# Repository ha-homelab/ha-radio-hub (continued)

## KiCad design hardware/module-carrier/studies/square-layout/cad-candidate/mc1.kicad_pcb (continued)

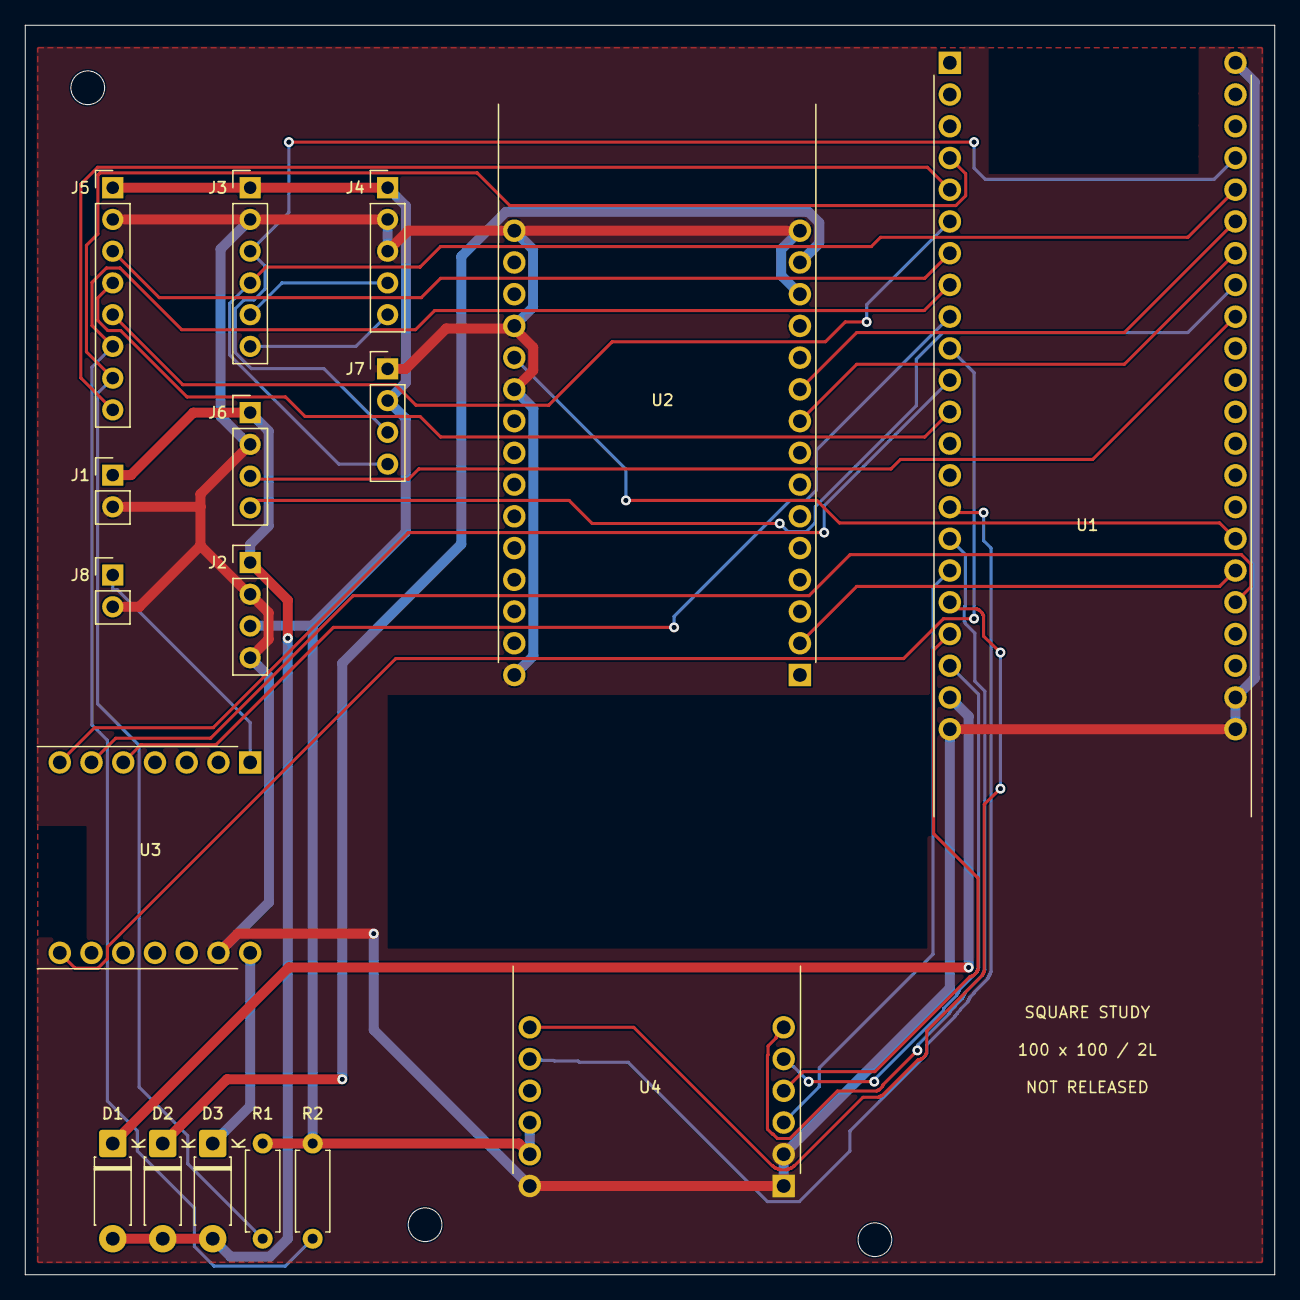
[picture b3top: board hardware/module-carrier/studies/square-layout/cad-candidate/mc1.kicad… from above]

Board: 2 copper layers, 100.0 x 100.0 mm, 20 parts (0 on the bottom side), 33 nets.

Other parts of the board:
H1, H2, H3: M2.5 NYLON NPTH

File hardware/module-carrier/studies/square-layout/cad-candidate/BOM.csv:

Reference,Quantity,Part / module,Carrier footprint,Side,Assembly note,Source
U1,1,ESP32-S3-DevKitC-1-N8R8 v1.1,MC1:S3_DevKitC1_v11,Top,Factory male headers solder directly; 3V3 outputs NC; USB19/20 and bridge43/44 untouched; no sockets,https://dl.espressif.com/dl/schematics/esp_idf/DXF_ESP32-S3-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
U2,1,ESP32-H2-DevKitM-1-N4S,MC1:H2_DevKitM1,Top,RCP RX4 TX5; native USB and UART bridge pins untouched; 3V3/VBAT NC,https://dl.espressif.com/dl/schematics/esp32-h2-devkitm-1_v1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
U3,1,Seeed XIAO MG24 pre-soldered 102010690,MC1:XIAO_MG24,Top,External UART PC06/PC07; CTS PC04 RTS PC05; USB probe preserved; 3V3 OUT NC,https://files.seeedstudio.com/wiki/XIAO_MG24/Getting_Start/X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
U4,1,WIZ850io finished module,MC1:WIZ850io,Top,Direct factory pins; two1x6 at20.32 rowspacing; RJ45 faces BOTTOM with mouth y=102mm; NO PoE extraction;3.3V only,https://docs.wiznet.io/img/products/wiz850io/wiz850io_dimension.png
J1,1,FUSED ISOLATED 5V INPUT,MC1:PinHeader_1x02_P2.54mm_Vertical,Top,Offboard assembled active PoE splitter and fused 5V harness. No raw PoE voltage on carrier.,https://www.samtec.com/products/tsw
J2,1,D24V22F3 external assembled buck,MC1:PinHeader_1x04_P2.54mm_Vertical,Top,Harness interface only; pin1 buckVIN; pin2GND;pin3buckVOUT;pin4GND. Buck remains separate ready module.,https://www.samtec.com/products/tsw
J3,1,DFR0627 WK2132 ready module harness,MC1:PinHeader_1x06_P2.54mm_Vertical,Top,"Harness to DFR0627 I2C and UART1, no WK2132 SMD on carrier. J3.5=module TX1;J3.6=module RX1; IA1=1 IA0=1; register address 0x70, FIFO 0x71; verify physical markings.",https://wiki.dfrobot.com/dfr0627
J4,1,ZAC93 ready module harness,MC1:PinHeader_1x05_P2.54mm_Vertical,Top,Carrier1->ZACpin1;2->pin6;3->pin9;4->pin8RX;5->pin10TX. Different from ZAC physical header layout.,https://www.samtec.com/products/tsw
J5,1,CC1101 ready module harness,MC1:PinHeader_1x08_P2.54mm_Vertical,Top,3.3V; GDO0 open-drain TX with external4.7k pullup; GDO2 receiver.,https://www.samtec.com/products/tsw
J6,1,LD2450 radar harness,MC1:PinHeader_1x04_P2.54mm_Vertical,Top,Carrier3->radarRX;carrier4<-radarTX;5V supply;3.3V data.,https://www.samtec.com/products/tsw
J7,1,BME680 external pod harness,MC1:PinHeader_1x04_P2.54mm_Vertical,Top,"External pod,1GND2VDD3SDA4SCL;I2C pullups on modules;do notaddunreviewedpullups.",https://www.samtec.com/products/tsw
D1,1,1N5819 USB supply isolation,MC1:D_DO-41_SOD81_P7.62mm_Horizontal,Top,Cathodepad1->board5V;anodepad2->fused5Vbus. VerifyUSBprogrammingpowerpaths;forwarddropheadroom.,https://www.vishay.com/docs/88525/1n5817.pdf
D2,1,1N5819 USB supply isolation,MC1:D_DO-41_SOD81_P7.62mm_Horizontal,Top,Cathodepad1->board5V;anodepad2->fused5Vbus. VerifyUSBprogrammingpowerpaths;forwarddropheadroom.,https://www.vishay.com/docs/88525/1n5817.pdf
D3,1,1N5819 USB supply isolation,MC1:D_DO-41_SOD81_P7.62mm_Horizontal,Top,Cathodepad1->board5V;anodepad2->fused5Vbus. VerifyUSBprogrammingpowerpaths;forwarddropheadroom.,https://www.vishay.com/docs/88525/1n5817.pdf
R1,1,4.7k RF GDO0 pull-up,MC1:R_Axial_DIN0207_L6.3mm_D2.5mm_P7.62mm_Horizontal,Top,,https://www.vishay.com/docs/28729/mrs16.pdf
R2,1,10k RF CS idle pull-up,MC1:R_Axial_DIN0207_L6.3mm_D2.5mm_P7.62mm_Horizontal,Top,,https://www.vishay.com/docs/28729/mrs16.pdf
J8,1,XIAO BOOT service short to GND,MC1:PinHeader_1x02_P2.54mm_Vertical,Top,Temporary short D0/PC00 to GND while resetting XIAO for recovery. Normally OPEN.,https://www.samtec.com/products/tsw

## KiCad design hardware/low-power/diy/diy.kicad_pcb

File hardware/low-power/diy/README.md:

# LP-D0: single-sided, wire-assisted DIY carrier

<!-- MC2-CURRENT-DESIGN -->
> **Current build: [MC2 — three external antennas](../../../docs/external-antennas.md).** This page retains an earlier design or evaluation for reference. Its board images, pin maps, enclosure fit and alternative BOMs are not the current MC2 build.

LP-D0 is a prototype for laser toner transfer and manual drilling. It implements the LP-P0 electrical contract on a 190 × 145 mm low-voltage backplane. The required assembly includes bottom copper **and insulated wire links**. It is not a one-layer redesign of the RF modules themselves, and no assembled D0 has been electrically tested yet.

The board accepts only isolated, regulated 5 V. The PoE front end and Pololu D24V22F3 regulator stay external. Never connect an Ethernet PoE pair or 48 V to this PCB. The nominal design ceiling remains 1 A at the 5 V input; actual startup voltage drop and temperature must be measured.

## What can be made with toner transfer

D0 uses 0.6 mm signal tracks, 1.2 mm supply/return tracks, nominal 0.5 mm copper clearance, and 2 mm through-hole lands. All copper tracks are on B.Cu. KiCad represents through-hole pads with annuli on both outer layers; **only the bottom annuli are fabricated**. There are no plated vias, no hidden top copper traces, and no electrical dependence on hole plating. Through-hole components and T-numbered wire holes are soldered on the copper side. The explicitly identified E-numbered joints instead solder to exposed raised-adapter header pins above the board; they do not add a drilled hole.

C0 is a two-layer, mixed SMT/through-hole carrier; printing only its bottom layer would omit connections. M0 has a fine-pitch MGM240P footprint, ground planes and an antenna keepout: order it from a PCB manufacturer. I0 is a four-layer integrated design and is unsuitable for this home process. Existing enclosure mounting patterns do not match D0.

## Purchased fine-pitch assemblies are still necessary

- U1 is SC16IS752IPW,128 soldered to the **TSSOP side** of an [Adafruit 1208 adapter](https://www.adafruit.com/product/1208), with two 14-pin headers. Looking at the populated TSSOP face, pin 1 is upper-left, pin 14 lower-left, pin 15 lower-right and pin 28 upper-right. Row separation is 15.24 mm and pitch 2.54 mm. The blank adapter does not include the IC or headers.
- U2 is TPS3808G33DBVR on the SOT23-6 side of an [Adafruit 1230 adapter](https://www.adafruit.com/product/1230), with two 3-pin headers. Pin1/2/3 run down the left; 6/5/4 down the right. Row separation 7.62 mm; pitch 2.54 mm. Do not populate the two reverse-side transistor sites. Stock may vary; a different adapter requires matching its pin map and dimensions.
- Keep both adapter PCBs at least 6 mm above D0; some insulated links may pass underneath. Fit and inspect these links before soldering the adapter in place. Use [Adafruit 400 extra-long headers](https://www.adafruit.com/product/400), cut to two 14-pin and two 3-pin lengths (one five-strip pack supplies both adapters). Its [manufacturer drawing](https://cdn-shop.adafruit.com/datasheets/18072.pdf) specifies 0.64 mm square pins, 7.73 mm on each side of a 2.54 mm insulator. Rest the insulator on D0, set the adapter underside 6 mm above D0, solder and trim the long tails. Availability must be checked before ordering.
- The populated [M0 adapter](../carrier/mg24-adapter/README.md) is mandatory for MGM240PA22VNA3. It contains the module decoupling, BOOT and SWD service connections. A bare MGM240P cannot plug into J6.
- S3/H2 development boards, WIZ850io, ZAC93, CC1101, LD2450 and BME680 connect through the named harnesses. This PCB does not invent pin positions for unknown module revisions. Use the verified GPIO/net labels, not guessed connector geometry.

The adapter mating geometry was checked against [Adafruit's published CAD at a fixed commit](https://github.com/adafruit/Adafruit-SMT-Breakout-PCBs/tree/dbd7a1928c2b668a9edf3d53277063eac4c3e938). U1/U2 still require fine-pitch soldering by the builder or an assembly service. The household-iron process applies to D0 alone.

## Files and assembly

- `diy.kicad_sch`, `diy.kicad_pcb`, `diy.kicad_pro`: native connected assembly schematic and PCB.
- `logical-netlist.json`: original electrical net names and physical part pins.
- `assembly-netlist.json`: bottom-copper islands plus actual off-board wire components W1…Wn.
- `connectors.json`: every connector pin, remote destination and actual board coordinates.
- `assembly-bom.csv`, `harness-bom.csv`: board parts, adapters, mating housings, contacts and materials.
- `jumpers.json`, `jumpers.csv`: every insulated link, AWG, terminal holes, route and cut length. The route is a top-view assembly guide, not copper artwork.
- `drill.csv`: all manually drilled holes in top-view coordinates.
- `print/`: printable transfer, inspection, drilling and assembly documents generated by the dedicated print exporter.

J1–J9 preserve C0's electrical pin numbering. J3 is **not a Raspberry Pi GPIO connector**. J10 changes physically from JST SH to through-hole JST XH, retaining 1=GND / 2=+3V3 / 3=SDA / 4=SCL. Splice to a factory QT cable and continuity-test each conductor. Every cable mating-face view is mirrored relative to the PCB component view; use molded circuit numbers and the square pin 1 land.

For F1 use Littelfuse 022901.5MXP, a 1.5 A slow-blow 2AG cartridge, in the external 01500274Z holder. Adapt the holder's 16 AWG leads to short 22 AWG insulated tails for the 1.1 mm F1 holes; cover the splices and strain-relieve the holder. The manufacturer [catalog](https://www.littelfuse.com/assetdocs/powr-gard-catalog?assetguid=85d36235-a32b-4608-bfed-f9878aa43af0) identifies the 229 series’ 125 VDC rating. The [holder datasheet](https://www.littelfuse.com/assetdocs/fuse-holder-150-datasheet?assetguid=662e5ae4-2c3a-4d7a-8642-e7d9db02703d) specifies 2AG/5×20 compatibility. This does not change D0's **5 V-only** input limit.

Use insulated AWG 24 for power/return jumpers and AWG 26 for signal links. At most two stripped ends share a 1.1 mm terminal hole; trial-fit wire and drill before making the whole board. The cut schedule includes the projected routed length plus 14 mm, with an additional 4 mm for each raised E joint; strip 5 mm at each end and trim the solder tails after assembly. Do not use bare jumpers where paths cross. Keep insulation against the board, avoiding conductive contact with headers, adapter pads or other wires. Support externally connected wires so a pull cannot lift a copper land.

E-numbered endpoints identify a specific U1/U2 header pin, not a new pad. Solder a single wire to its exposed shaft at **4 mm above D0**, before placing the adapter at its required **6 mm underside height**. The first/last 3 mm of that wire passes over the header insulator at the raised height, then descends. Keep the joint compact, insulated from adjacent pins and strain-relieved. Confirm the actual 2 mm space below the daughterboard is sufficient for the joint and wire before final soldering; this fit is not yet physically tested. The board-level adapter courtyards represent the header strips, while assembly drawings retain the full elevated board outlines.

## Firmware and physical acceptance

No GPIO or serial assignment changes. The supplied low-power firmware currently uses 10 MHz W5500 SPI and 4 MHz for the shared CC1101/SC16 bus. D0 has no controlled-impedance routing or ground plane; clock frequencies are not proof that its assembled wires will be reliable. Keep external SPI harnesses at or below an initial 50 mm, retain the interleaved returns in J3, pair each clock/data group with a short return, and measure SPI edges and error behavior with the full load. This starting length is a prototype constraint, not a validated signal-integrity guarantee. The 3 W AC objective is also unmeasured for D0. If a lower SPI rate is required, use an explicit D0 configuration change and repeat the firmware build and throughput tests; do not silently edit the common profile.

Before installing modules: inspect the toner result under magnification; verify no copper bridges; continuity-test all nets against the schematic, including every W link; check 5 V/3.3 V/GND isolation; confirm F1 and regulator polarity. Power from a current-limited 5 V source first, verify 3.3 V at every connector, then add modules in stages. Check U1 crystal startup, its 115200 baud UART, IRQ handling, H2 reset/BOOT, Zigbee RTS/CTS and CC1101 transmit/receive arbitration. Repeat the existing hub acceptance tests with the final enclosure and radios active. Radio antenna spacing and the M0 keepout remain unchanged.

A passed CAD check cannot establish toner adhesion, actual etched track width, hand-drilled annular rings, solder quality, antenna performance, regulatory compliance or production readiness. The board is a workshop prototype, not a validated product for sale.

## Reproduce and validate

Run from the repository root with KiCad 10's Python (which supplies `pcbnew`):

```sh
python3 hardware/low-power/diy/generate.py
python3 -m unittest discover -s hardware/low-power/diy -p 'test_*.py'
python3 hardware/low-power/diy/validate.py --kicad-cli kicad-cli --check-hashes --out /tmp/d0-check
```

`routing-plan.json` is the reviewed geometric input. Regeneration uses it directly and never reruns an autorouter. Optional route-authoring tools are `prepare.py`, `capture_routing.py`, `plan_wires.py` and `complete_wires.py`; they write exploratory files under ignored `.build/`. Their intermediate F.Cu geometry must never be sent to a fabricator or printed for transfer. The final validator calculates copper contact from the actual PCB, joins only the numbered assembly wires, and compares the result to the original pin-level contract. Native ERC/DRC alone is insufficient because an intentionally split island net can be internally connected while the required physical wire is missing.

The released D0 snapshot has 636 bottom tracks, 100 dedicated wire holes, 54 insulated links and one raised joint E1 at U1.11. Native ERC, DRC, schematic parity and unconnected checks report zero violations. The independent graph verifies all 195 component pins across 44 logical nets. These are CAD results, not measurements of a constructed board.

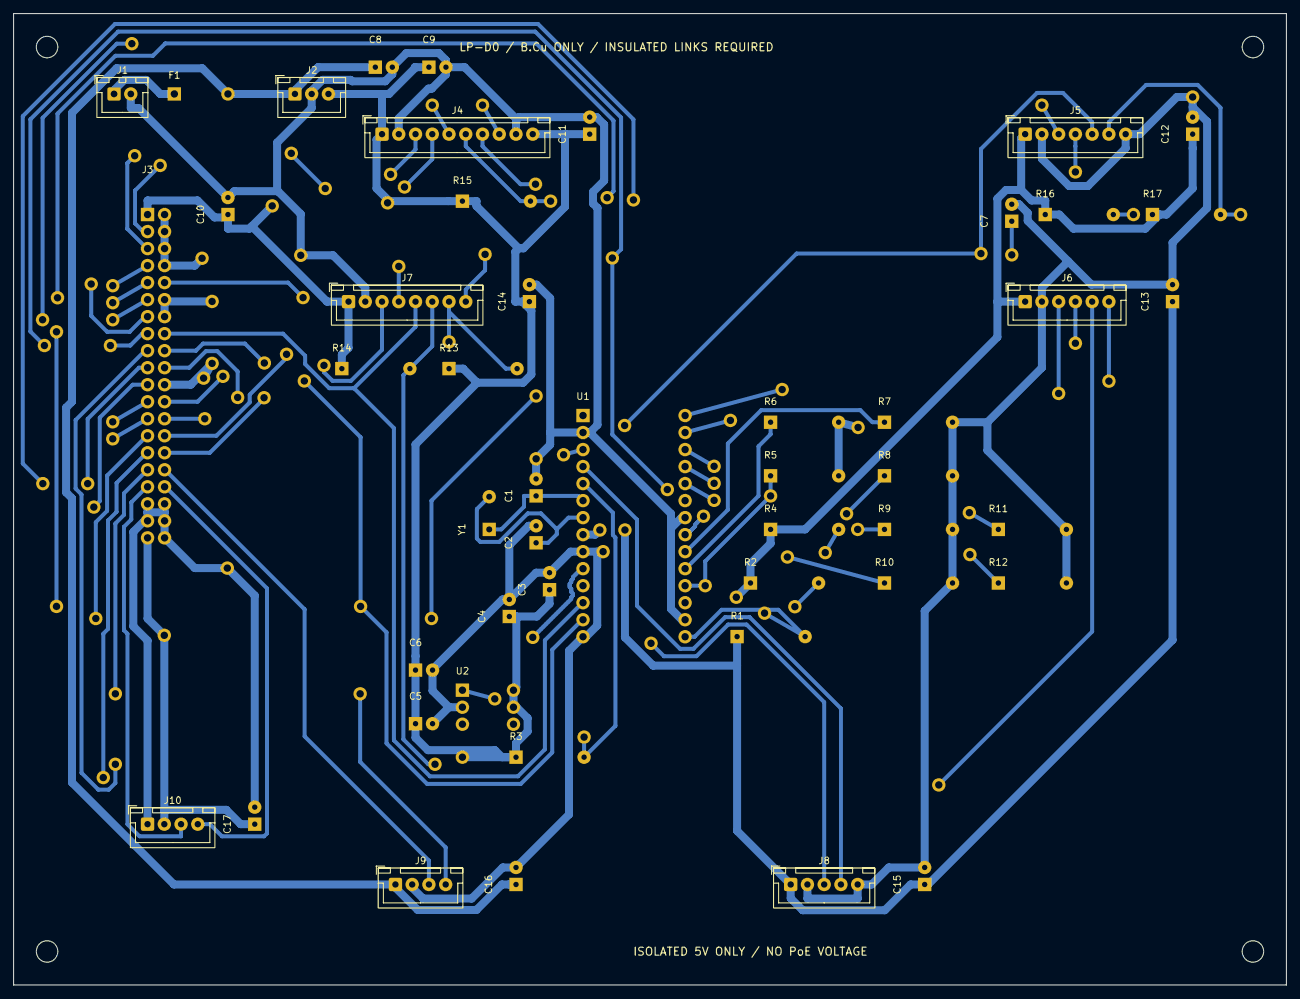
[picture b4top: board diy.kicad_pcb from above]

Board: 2 copper layers, 190.0 x 145.0 mm, 152 parts (0 on the bottom side), 97 nets.

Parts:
C1: 22pF; Radial_C_P2.54
C2: 33pF; Radial_C_P2.54
C3, C5, C10, C11, C12, C13, C14, C15, C16, C17: 100nF; Radial_C_P2.54
C4, C7: 1uF; Radial_C_P2.54
C6: 1nF; Radial_C_P2.54
C8, C9: 22uF; Radial_C_P2.54
F1: Littelfuse 022901.5MXP; FuseHarness
H1, H2, H3, H4: M3 manually drilled
J1: B2B-XH-A; JST_XH_B2B-XH-A_1x02_P2.50mm_Vertical
J2: B3B-XH-A; JST_XH_B3B-XH-A_1x03_P2.50mm_Vertical
J3: 61204021621; Wurth_61204021621
J4: B10B-XH-A; JST_XH_B10B-XH-A_1x10_P2.50mm_Vertical
J5: B7B-XH-A; JST_XH_B7B-XH-A_1x07_P2.50mm_Vertical
J6: B6B-XH-A; JST_XH_B6B-XH-A_1x06_P2.50mm_Vertical
J7: B8B-XH-A; JST_XH_B8B-XH-A_1x08_P2.50mm_Vertical
J8: B5B-XH-A; JST_XH_B5B-XH-A_1x05_P2.50mm_Vertical
J9, J10: B4B-XH-A; JST_XH_B4B-XH-A_1x04_P2.50mm_Vertical
R1: 1k; Axial_R_P10.16
R2, R3, R4, R14, R15, R16, R17: 10k; Axial_R_P10.16
R5, R6, R7, R8, R9, R10, R11, R12: 100k; Axial_R_P10.16
R13: 4.7k; Axial_R_P10.16
T1, T2, T3, T4, T5, T6, T7, T8, T9, T10, T11, T12, T13, T14, T15, T16, T17, T18, T19, T20, T21, T22, T23, T24, T25, T26, T27, T28, T29, T30, T31, T32, T33, T34, T35, T36, T37, T38, T39, T40, T41, T42, T43, T44, T45, T46, T47, T48, T49, T50, T51, T52, T53, T54, T55, T56, T57, T58, T59, T60, T61, T62, T63, T64, T65, T66, T67, T68, T69, T70, T71, T72, T73, T74, T75, T76, T77, T78, T79, T80, T81, T82, T83, T84, T85, T86, T87, T88, T89, T90, T91, T92, T93, T94, T95, T96, T97, T98, T99, T101: Insulated wire terminal hole; WireTerminal
U1: SC16IS752IPW,128; Adafruit1208_TSSOP28
U2: TPS3808G33DBVR; Adafruit1230_SOT23_6
Y1: AB-3.6864MHZ-B2; HC49U

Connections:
/+3V3__1: C10.1, J3.1, J7.1, R14.1, T2.1
/+3V3__2: C3.1, C4.1, C5.1, C6.1, C9.1, C11.1, C14.1, J2.3, J4.1, J4.10, R3.1, R13.1, R15.1, T3.1, T79.1, U2.5, U2.6
/+3V3__3: C12.1, J5.1, J6.1, R2.1, R4.1, R16.1, R17.1, T78.1
/+3V3__4: C13.1, C15.1, J8.1, R1.1, T5.1
/+3V3__5: C17.1, J3.39, J10.2, T1.1
/+3V3__6: T4.1, U1.8
/+5V_IN__1: F1.1, J1.1
/+5V__1: C8.1, C16.1, F1.2, J2.1, J9.1
/GND__1: C1.2, C8.2, C9.2, C10.2, C11.2, C14.2, J1.2, J2.2, J4.2, J4.9, J7.2, T10.1, T11.1, U1.2, U1.16, U1.22
/GND__2: C7.2, C12.2, C13.2, C15.2, J5.2, J5.7, J6.2, J8.2, J8.5, R7.2, R8.2, R9.2, R10.2, R11.2, R12.2, T13.1
/GND__3: C2.2, C3.2, C4.2, C5.2, C6.2, C16.2, J9.2, T12.1, U1.9, U1.14, U2.2
/GND__4: C17.2, J3.35, J3.36, J3.37, J3.38, J3.40, J10.1, T9.1
/GND__5: J3.12, J3.14, T7.1
/GND__6: J3.2, J3.4, J3.6, J3.8, T6.1
/GND__7: J3.22, T8.1, T81.1
/GND__8: R5.2, R6.2, T80.1
/bme680_scl__1: J3.34, J10.4
/bme680_sda__1: J3.33, J10.3
/cc1101_cs__1: J3.17, T14.1
/cc1101_cs__2: J7.6, R14.2, T15.1
/cc1101_gdo0_tx__1: J3.18, T16.1
/cc1101_gdo0_tx__2: J7.7, R13.2, T82.1
/cc1101_gdo2_rx__1: J3.19, T18.1
/cc1101_gdo2_rx__2: J7.8, T19.1
/cc1101_gdo2_rx__3: T17.1, T20.1
/gpio0_unused__1: R5.1, T21.1, T22.1, U1.18
/gpio1_unused__1: R6.1, U1.19
/gpio2_unused__1: R7.1, U1.20
/gpio3_unused__1: R8.1, T83.1
/gpio3_unused__2: T84.1, U1.21
/gpio4_unused__1: R9.1, T85.1
/gpio4_unused__2: T86.1, U1.25
/gpio5_unused__1: R10.1, T87.1
/gpio5_unused__2: T88.1, U1.26
/gpio6_unused__1: R11.1, T89.1
/gpio6_unused__2: T90.1, U1.27
/gpio7_unused__1: R12.1, T91.1
/gpio7_unused__2: T92.1, U1.28
/h2_boot__1: J3.26, T23.1
/h2_boot__2: J5.6, R17.2, T24.1
/h2_reset__1: C7.1, T28.1
/h2_reset__2: J3.25, T25.1
/h2_reset__3: J5.5, T26.1, T27.1
/h2_reset__4: R16.2, T29.1
/h2_rx__1: J3.24, T30.1
/h2_rx__2: J5.4, T31.1
/h2_tx__1: J3.23, T32.1
/h2_tx__2: J5.3, T33.1
/ld2450_rx__1: J3.32, J9.3
/ld2450_tx__1: J3.31, T34.1
/ld2450_tx__2: J9.4, T35.1
/mg24_cts__1: J3.30, T36.1
/mg24_cts__2: J6.6, T37.1
/mg24_rts__1: J3.29, T38.1
/mg24_rts__2: J6.5, T39.1
/mg24_rx__1: J3.28, T40.1
/mg24_rx__2: J6.4, T41.1
/mg24_tx__1: J3.27, T42.1
/mg24_tx__2: J6.3, T45.1
/mg24_tx__3: T43.1, T44.1
/rxb_unused__1: R4.2, T93.1
/rxb_unused__2: T94.1, U1.24
/sc16_cs__1: J3.20, T46.1
/sc16_cs__2: R2.2, T95.1
/sc16_cs__3: T96.1, U1.10
/sc16_irq__1: J3.21, T47.1
/sc16_irq__2: R1.2, T97.1, U1.15
/sc16_reset__1: R3.2, T98.1, U1.5
/sc16_reset__2: T99.1, U2.1
/shared_spi_miso__1: J3.16, J7.5, U1.12
/shared_spi_mosi__1: J3.15, T49.1
/shared_spi_mosi__2: J7.4, T50.1
/shared_spi_mosi__4: T48.1, T51.1, T52.1
/shared_spi_sclk__1: J3.13, T55.1
/shared_spi_sclk__2: J7.3, T57.1
/shared_spi_sclk__3: T56.1, T58.1, U1.13
/shared_spi_sclk__4: T53.1, T54.1
/w5500_cs__1: J3.9, T60.1
/w5500_cs__2: J4.6, R15.2, T61.1
/w5500_cs__3: T59.1, T62.1
/w5500_irq__1: J3.10, T63.1
/w5500_irq__2: J4.7, T64.1
/w5500_miso__1: J3.7, T65.1
/w5500_miso__2: J4.5, T66.1
/w5500_mosi__1: J3.5, T67.1
/w5500_mosi__2: J4.4, T70.1
/w5500_mosi__3: T68.1, T69.1
/w5500_reset__1: J3.11, T72.1
/w5500_reset__2: J4.8, T74.1
/w5500_reset__3: T71.1, T73.1
/w5500_sclk__1: J3.3, T75.1
/w5500_sclk__2: J4.3, T76.1
/xtal1__1: C1.1, U1.6, Y1.1
/xtal2__1: C2.1, U1.7, Y1.2
/zac93_rx__1: J8.4, U1.4
/zac93_tx__1: J8.3, T77.1
/zac93_tx__2: T101.1, U1.3

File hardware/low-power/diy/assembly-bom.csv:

Reference,Quantity,Manufacturer part / value,Footprint,Note,Source
J1,1,B2B-XH-A,Connector_JST:JST_XH_B2B-XH-A_1x02_P2.50mm_Vertical,Isolated regulated 5V input,https://www.jst-mfg.com/product/pdf/eng/eXH.pdf
J2,1,B3B-XH-A,Connector_JST:JST_XH_B3B-XH-A_1x03_P2.50mm_Vertical,External D24V22F3 buck,https://www.jst-mfg.com/product/pdf/eng/eXH.pdf
J3,1,61204021621,DIY:Wurth_61204021621,S3 keyed 40-position IDC harness; NOT Raspberry Pi compatible,https://www.we-online.com/components/products/datasheet/6120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
J4,1,B10B-XH-A,Connector_JST:JST_XH_B10B-XH-A_1x10_P2.50mm_Vertical,WIZ850io Ethernet module,https://www.jst-mfg.com/product/pdf/eng/eXH.pdf
J5,1,B7B-XH-A,Connector_JST:JST_XH_B7B-XH-A_1x07_P2.50mm_Vertical,H2 Thread RCP,https://www.jst-mfg.com/product/pdf/eng/eXH.pdf
J6,1,B6B-XH-A,Connector_JST:JST_XH_B6B-XH-A_1x06_P2.50mm_Vertical,MG24 Zigbee NCP,https://www.jst-mfg.com/product/pdf/eng/eXH.pdf
J7,1,B8B-XH-A,Connector_JST:JST_XH_B8B-XH-A_1x08_P2.50mm_Vertical,CC1101 RF module,https://www.jst-mfg.com/product/pdf/eng/eXH.pdf
J8,1,B5B-XH-A,Connector_JST:JST_XH_B5B-XH-A_1x05_P2.50mm_Vertical,ZAC93 Z-Wave module,https://www.jst-mfg.com/product/pdf/eng/eXH.pdf
J9,1,B4B-XH-A,Connector_JST:JST_XH_B4B-XH-A_1x04_P2.50mm_Vertical,LD2450 radar,https://www.jst-mfg.com/product/pdf/eng/eXH.pdf
J10,1,B4B-XH-A,Connector_JST:JST_XH_B4B-XH-A_1x04_P2.50mm_Vertical,"TH XH to factory STEMMA QT cable; same logical order as C0, mechanically NOT a QT socket.",https://www.jst-mfg.com/product/pdf/eng/eXH.pdf
F1,1,Littelfuse 022901.5MXP,DIY:FuseHarness,1.5A slow-blow 2AG cartridge in external01500274Z holder. Holder leads adapt to22AWG at F1 holes; insulate splices. <=1A continuous design. Do not bridge.,https://www.littelfuse.com/assetdocs/powr-gard-catalog?asset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
U1,1,"SC16IS752IPW,128",DIY:Adafruit1208_TSSOP28,"SC16IS752IPW,128 soldered to factory Adafruit1208 TSSOP side; pin1 adapter orientation verified from published CAD; no SOIC chip. Solder 2x14 male headers to adapter.",https://www.adafruit.com/product/1208
U2,1,TPS3808G33DBVR,DIY:Adafruit1230_SOT23_6,"TPS3808G33DBVR soldered to factory Adafruit1230 SOT23-6 adapter, two 1x3 male headers. Do not populate reverse-side transistor footprints.",https://www.adafruit.com/product/1230
Y1,1,AB-3.6864MHZ-B2,DIY:HC49U,"Through-hole HC49/U 3.6864MHz18pF; 4.88mm lead pitch; initial22/33pF loads, validate oscillation/frequency on hardware.",https://abracon.com/Resonators/ab.pdf
R1,1,1k,DIY:Axial_R_P10.16,"Axial 1%0.25W resistor, body<=6.8x2.5mm, leads formed to10.16mm pitch.",
R2,1,10k,DIY:Axial_R_P10.16,"Axial 1%0.25W resistor, body<=6.8x2.5mm, leads formed to10.16mm pitch.",
R3,1,10k,DIY:Axial_R_P10.16,"Axial 1%0.25W resistor, body<=6.8x2.5mm, leads formed to10.16mm pitch.",
R4,1,10k,DIY:Axial_R_P10.16,"Axial 1%0.25W resistor, body<=6.8x2.5mm, leads formed to10.16mm pitch.",
R5,1,100k,DIY:Axial_R_P10.16,"Axial 1%0.25W resistor, body<=6.8x2.5mm, leads formed to10.16mm pitch.",
R6,1,100k,DIY:Axial_R_P10.16,"Axial 1%0.25W resistor, body<=6.8x2.5mm, leads formed to10.16mm pitch.",
R7,1,100k,DIY:Axial_R_P10.16,"Axial 1%0.25W resistor, body<=6.8x2.5mm, leads formed to10.16mm pitch.",
R8,1,100k,DIY:Axial_R_P10.16,"Axial 1%0.25W resistor, body<=6.8x2.5mm, leads formed to10.16mm pitch.",
R9,1,100k,DIY:Axial_R_P10.16,"Axial 1%0.25W resistor, body<=6.8x2.5mm, leads formed to10.16mm pitch.",
R10,1,100k,DIY:Axial_R_P10.16,"Axial 1%0.25W resistor, body<=6.8x2.5mm, leads formed to10.16mm pitch.",
R11,1,100k,DIY:Axial_R_P10.16,"Axial 1%0.25W resistor, body<=6.8x2.5mm, leads formed to10.16mm pitch.",
R12,1,100k,DIY:Axial_R_P10.16,"Axial 1%0.25W resistor, body<=6.8x2.5mm, leads formed to10.16mm pitch.",
R13,1,4.7k,DIY:Axial_R_P10.16,"Axial 1%0.25W resistor, body<=6.8x2.5mm, leads formed to10.16mm pitch.",
R14,1,10k,DIY:Axial_R_P10.16,"Axial 1%0.25W resistor, body<=6.8x2.5mm, leads formed to10.16mm pitch.",
R15,1,10k,DIY:Axial_R_P10.16,"Axial 1%0.25W resistor, body<=6.8x2.5mm, leads formed to10.16mm pitch.",
R16,1,10k,DIY:Axial_R_P10.16,"Axial 1%0.25W resistor, body<=6.8x2.5mm, leads formed to10.16mm pitch.",
R17,1,10k,DIY:Axial_R_P10.16,"Axial 1%0.25W resistor, body<=6.8x2.5mm, leads formed to10.16mm pitch.",
C1,1,22pF,DIY:Radial_C_P2.54,"Radial ceramic >=10V, body<=5x3mm, C0G for crystal loads; X7R otherwise. Form leads to2.54mm pitch; no adjacent lead shorts.",
C2,1,33pF,DIY:Radial_C_P2.54,"Radial ceramic >=10V, body<=5x3mm, C0G for crystal loads; X7R otherwise. Form leads to2.54mm pitch; no adjacent lead shorts.",
C3,1,100nF,DIY:Radial_C_P2.54,"Radial ceramic >=10V, body<=5x3mm, C0G for crystal loads; X7R otherwise. Form leads to2.54mm pitch; no adjacent lead shorts.",
C4,1,1uF,DIY:Radial_C_P2.54,"Radial ceramic >=10V, body<=5x3mm, C0G for crystal loads; X7R otherwise. Form leads to2.54mm pitch; no adjacent lead shorts.",
C5,1,100nF,DIY:Radial_C_P2.54,"Radial ceramic >=10V, body<=5x3mm, C0G for crystal loads; X7R otherwise. Form leads to2.54mm pitch; no adjacent lead shorts.",
C6,1,1nF,DIY:Radial_C_P2.54,"Radial ceramic >=10V, body<=5x3mm, C0G for crystal loads; X7R otherwise. Form leads to2.54mm pitch; no adjacent lead shorts.",
C7,1,1uF,DIY:Radial_C_P2.54,"Radial ceramic >=10V, body<=5x3mm, C0G for crystal loads; X7R otherwise. Form leads to2.54mm pitch; no adjacent lead shorts.",
C8,1,22uF,DIY:Radial_C_P2.54,"22uF >=10V radial electrolytic, body<=5mm, pin1 positive. Form leads to2.54mm pitch; no adjacent lead shorts.",
C9,1,22uF,DIY:Radial_C_P2.54,"22uF >=10V radial electrolytic, body<=5mm, pin1 positive. Form leads to2.54mm pitch; no adjacent lead shorts.",
C10,1,100nF,DIY:Radial_C_P2.54,"Radial ceramic >=10V, body<=5x3mm, C0G for crystal loads; X7R otherwise. Form leads to2.54mm pitch; no adjacent lead shorts.",
C11,1,100nF,DIY:Radial_C_P2.54,"Radial ceramic >=10V, body<=5x3mm, C0G for crystal loads; X7R otherwise. Form leads to2.54mm pitch; no adjacent lead shorts.",
C12,1,100nF,DIY:Radial_C_P2.54,"Radial ceramic >=10V, body<=5x3mm, C0G for crystal loads; X7R otherwise. Form leads to2.54mm pitch; no adjacent lead shorts.",
C13,1,100nF,DIY:Radial_C_P2.54,"Radial ceramic >=10V, body<=5x3mm, C0G for crystal loads; X7R otherwise. Form leads to2.54mm pitch; no adjacent lead shorts.",
C14,1,100nF,DIY:Radial_C_P2.54,"Radial ceramic >=10V, body<=5x3mm, C0G for crystal loads; X7R otherwise. Form leads to2.54mm pitch; no adjacent lead shorts.",
C15,1,100nF,DIY:Radial_C_P2.54,"Radial ceramic >=10V, body<=5x3mm, C0G for crystal loads; X7R otherwise. Form leads to2.54mm pitch; no adjacent lead shorts.",
C16,1,100nF,DIY:Radial_C_P2.54,"Radial ceramic >=10V, body<=5x3mm, C0G for crystal loads; X7R otherwise. Form leads to2.54mm pitch; no adjacent lead shorts.",
C17,1,100nF,DIY:Radial_C_P2.54,"Radial ceramic >=10V, body<=5x3mm, C0G for crystal loads; X7R otherwise. Form leads to2.54mm pitch; no adjacent lead shorts.",
